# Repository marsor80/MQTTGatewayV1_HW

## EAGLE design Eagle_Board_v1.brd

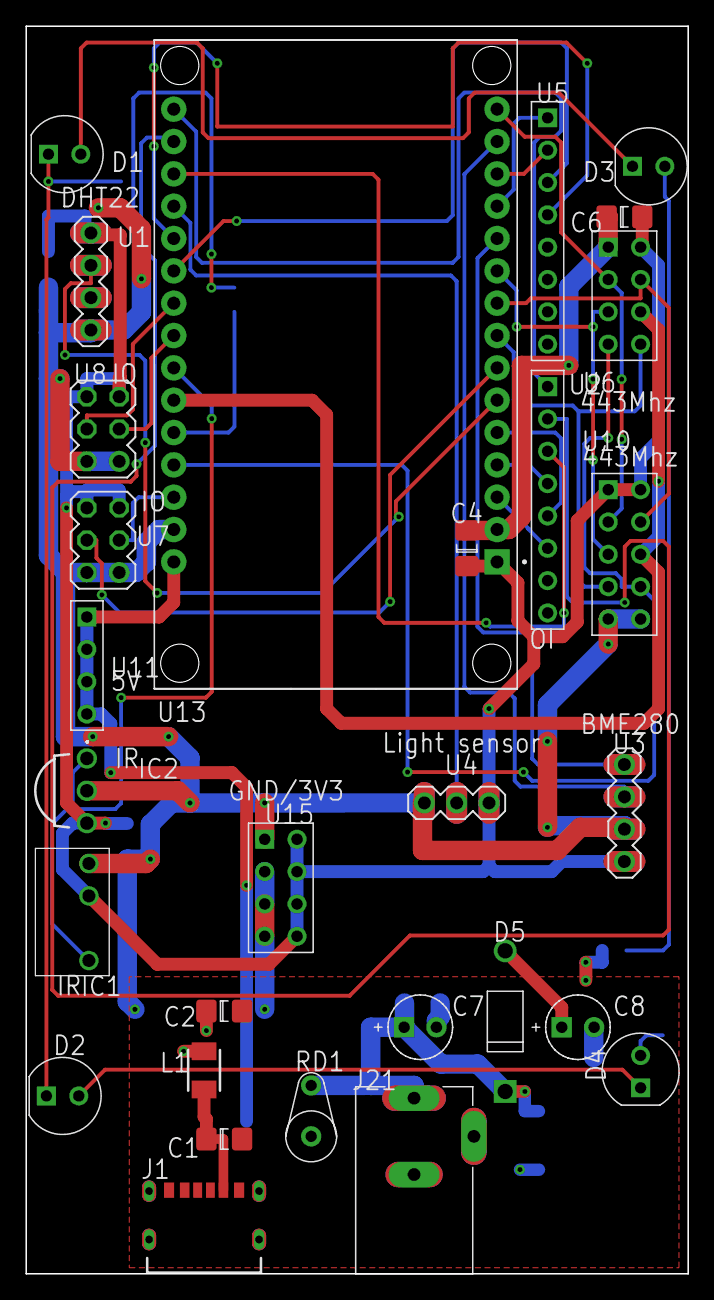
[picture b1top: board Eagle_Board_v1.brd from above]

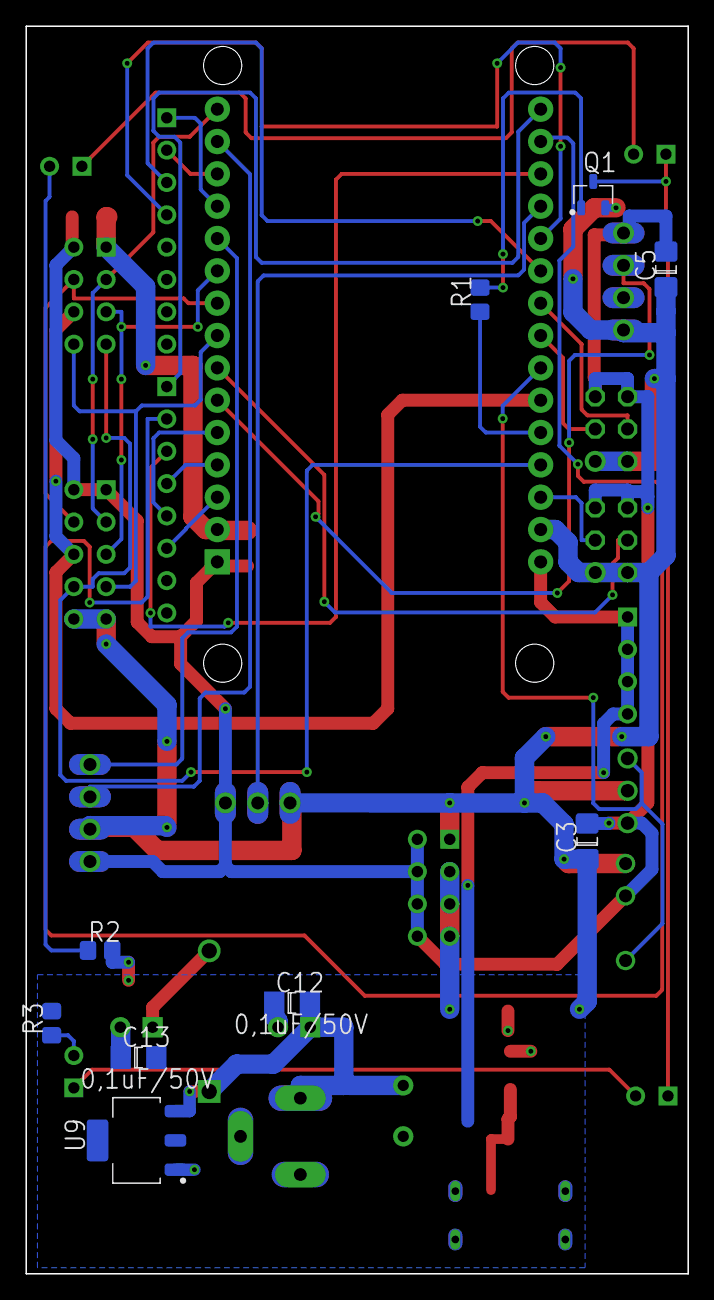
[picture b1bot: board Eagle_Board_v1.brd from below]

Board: 2 copper layers, 52.0 x 98.0 mm, 38 parts (9 on the bottom side), 37 nets.

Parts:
C1, C2: CAP_1206
C3, C5: CAP_1206; CAP_1206_C3
C4: CAP_1206; CAP_1206_C4
C6: CAP_1206; CAP_1206_C6
C7: CAP100RP; CAPPR-2.54/5.08
C8: CAP100RP; CAPPR-2.54/5.08_C8
C12, C13: 0,1uF/50V; CAP_1206_C12
D1: LED-5MM ROUND RED; LED-5mm_Round_Red
D2: LED-5MM ROUND RED; LED-5mm_Round_Red_D2
D3: LED-5MM ROUND RED; LED-5mm_Round_Red_D3
D4: LED-5MM ROUND RED; LED-5mm_Round_Red_D4
D5: 1N4001; DO-41
IC1: IR; TSOP31236
IC2: IR; TSOP4856
J1: USB4125-GF-A-0190_REVA2; GCT_USB4125-GF-A-0190_REVA2
J21: PJ-017C; CUI_PJ-017C
L1: NLFV32T-3R3M-EF; INDM3225X240N
Q1: BC848BLT3G; SOT23-3P95_240X110L43X44N
R1, R2, R3: RES_0805
RD1: RESISTOR DIODE ASSY; VR37_Vertical
U1: DHT22; MA04-1
U2: IO; HDR-1X8
U3: BME280; MA04-1_U3
U4: Light sensor; MA03-1
U5: HDR-1X8; HDR-1X8_U5
U6: 443Mhz; HDR-2X4
U7: IO; MA03-2
U8: IO; MA03-2_U8
U9: LT1117CST-5#PBF; SOT223-4P230_700X180L65X72N
U10: 443Mhz; HDR-2x5
U11: 5V; HDR-1X4
U13: ESP32-DEVKIT-V1; MODULE_ESP32_DEVKIT_V1
U15: GND/3V3; HDR-2X4_U15

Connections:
3v3: C3.2, C4.1, C5.2, C6.2, IC1.2, IC2.3, U1.4, U3.4, U4.3, U6.2, U7.5, U7.6, U8.5, U8.6, U10.1, U10.2, U13.1, U15.2, U15.4, U15.6, U15.8
5V: C2.1, C8.1, C13.2, D5.2, L1.2, R2.2, R3.2, U9.2, U9.4, U11.1, U11.2, U11.3, U11.4, U13.30
24V: C7.1, C12.2, D5.1, J21.1, RD1.2, U9.3
CSN: U6.8, U10.7, U13.8
DHT11/22: U1.3, U13.6
GDO0: U6.7, U10.8, U13.27
GDO2: U6.6, U10.6, U13.25
GND: C1.2, C2.2, C3.1, C4.2, C5.1, C6.1, C7.2, C8.2, C12.1, C13.1, IC1.1, IC2.2, J1.A12, J1.B12, J21.2, Q1.2, RD1.1, U1.1, U3.3, U4.1, U6.1, U7.1, U7.2, U8.1, U8.2, U9.1, U10.9, U10.10, U13.2, U13.29, U15.1, U15.3, U15.5, U15.7
MISO: U6.5, U10.5, U13.10
MOSI: U6.3, U10.3, U13.15
Net_0: D1.2, D3.1
Net_1: D2.2, D4.1
Net_2: D4.2, R3.1
Net_3: D3.2, R2.1
Net_6: C1.1, J1.A9, J1.B9, L1.1
Net_7: D1.1, D2.1, Q1.3
Net_8: Q1.1, R1.2
Net_27: U2.1, U13.16
Net_28: U2.2, U13.17
Net_29: U2.3, U13.18
Net_30: U2.4, U13.4
Net_31: U2.5, U13.5
Net_32: U2.6, U13.3
Net_33: U5.1, U13.12
Net_34: U5.2, U13.13
Net_35: U5.3, U13.21
Net_36: U5.4, U13.20
SCK: U6.4, U10.4, U13.9
SCL: U3.2, U13.14
SDA: U3.1, U13.11
io13: U7.3, U13.28
io17: U7.4, U13.7
io25: U8.3, U13.23
io33: U8.4, U13.22
ir_reciver_1: IC1.3, IC2.1, U13.24
ir_tr: R1.1, U13.26
light: U4.2, U13.19
